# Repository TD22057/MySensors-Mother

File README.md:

# MySensors Mother/Daughter board system

This repository contains the PCB design files, 3D renderings, and
software libraries to implement the
[MySensors](http:www.mysensors.org) mother/daughter board system
[described in this
thread](http://forum.mysensors.org/topic/2480/mother-daughter-board-system).

It's a mother/daughter board design using an RFM69 radio (though it
would be easy to change it to an NRF). I have about 10 sensors I need
to make and they're all similar, but not quite the same. This system
allows be to mix and match what I need for each application. It's
designed to be AC powered and uses a single case (see below) for all
of them (~$3/apiece for 10).

The main board has the basic components and supports two daughter
boards (roughly 25mm x 35mm) which plug into the side so the whole
assembly is basically flat (leaving more room in the case for the
switches, connectors, and LED's). An additional third daughter board
can be used for small boards mounted perpendicular to the main boards
(the sensor board below does that) or mounting over the top of the
arduino.

The main board contains:

- 3.3V Arduino Pro Mini
- RFM69 radio
   - side mount for external dipole antenna
   - interior mount with enough space for a helical antenna mounted
     parallel or perpendicular to the board
- 5V->3.3V power supply
- digital signing chip
- flash memory chip
- input and output shift registers
- headers for a switch, LED, and piezo buzzer
- header for SPI (MISO, MOSI, SCK) pins
- 2 side mounted daughter board headers with inputs and outputs from
  the shift registers
- 1 top mounted daughter board header with pins from the mini including
  D3 (IRQ), D5 and D6 (PWM), A3, A4 (SDA), and A5 (SCL)
- all components are top mounted for easier soldering and a bigger
  ground plane for better antenna performance

# Boards

Each daughter board header has 5V, 3.3V, ground, 3 input pins, and 3
output pins.  I've designed seven different daughter boards so far.   

- Valve/motor control board. I'm using this for articulated water
  valves for controlling leaks at the water heater, washing machine,
  etc.  It contains a L9110 motor controller, LED, and valve
  open/closed sensors.
- AC relay board. I'm using this to control simple AC load switching
  (in my case, a recirculation pump).  The board contains an
  opto-isolated AC relay with NO and NC terminals, 1 LED, and 2 sensor
  inputs with pull down resistors.
- DC relay board. I'm using this to control simple DC load switching
  (in my case, a triggering a garage door).  The board contains an
  opto-isolated DC relay with NO and NC terminals, 2 LED's, and 3 sensor
  inputs with pull down resistors.
- Protected input board. I'm using this to trigger when external
  security cameras and motion sensors trip (they both operate on 12V
  signals).  The board contains 3 opto-isolator circuits for
  triggering on 12V lines.
- Parking/RGB sensor board.  This board contains pins for an
  ultrasonic distance sensor and an RGB (neopixel) ring.  It includes
  5V/3.3V level shifting for the distance sensor.  This board must be
  connected to the 3'rd slot which interfaces directly with the
  Arduino pins because of the neopixel timing requirements.
- Sensor board.  3 sensor inputs with pull down resistors and 3 LED
  outputs with 1K resistors.  This is designed primarily for water
  leak detectors.  The rope leak sensor I'm using works better w/ 5V
  input and analog output so sensors can be fed with 5V or 3.3V and
  when connected in the 3'rd slot, they will output to the Arduino's
  analog pins.
- I2C board.  This is simple small board that adds multiple I2C pins.

Here's an image of the assembled boards:

# Ordering

The boards file contains the individual board designs (done in Eagle)
as well as panelized versions.  A single 10cm x 10cm panel contains 2
main boards, 1 each of the AC relay, DC relay, protected input,
parking board, and I2C board; 2 valve boards; and 3 sensor boards.  

# Project Case

The boards are designed to fit inside a specific case (size and
mounting holes) which can be [found
here](http://www.aliexpress.com/item/Wholesale-electrical-junction-box-10pcs-105-65-40mm-plastic-instrument-box-plastic-box-electronic-project-box/1986580384.html).
There are many options for ordering this case on AliExpress (various
quantities and vendors).  Searching for ["105\*65\*40mm"](http://www.aliexpress.com/af/105*65*40mm.html?ltype=wholesale&d=y&origin=n&isViewCP=y&catId=0&initiative_id=SB_20160206141640&SearchText=105*65*40mm) will
generally show them all.

# Software

The lib directory contains a class for each board.  Each child board
class is constructed by passing it a structure from the main board
class which defines which slot it's plugged in to.  The boards (mother
and children) all contain elements for manipulating their components
(LED's, relays, sensors, etc) which abstract away the method by which
their connected (call sensor.led[0].on() to turn on the 0'th LED of a
sensor board) which makes writing the final sketches which use the
boards very easy.

The software does depend on my [arduino-core library
classes](https://github.com/TD22057/TD-Arduino-Core).

# Licenses

All the software in this repository is covered by the GPL-V3 license
(see [LICENSE-software](LICENSE-software)).

All the hardare in this repository is covered by the CERN Open
Hardware Licence v1.2 (see [LICENSE-hardware](LICENSE-hardware)).

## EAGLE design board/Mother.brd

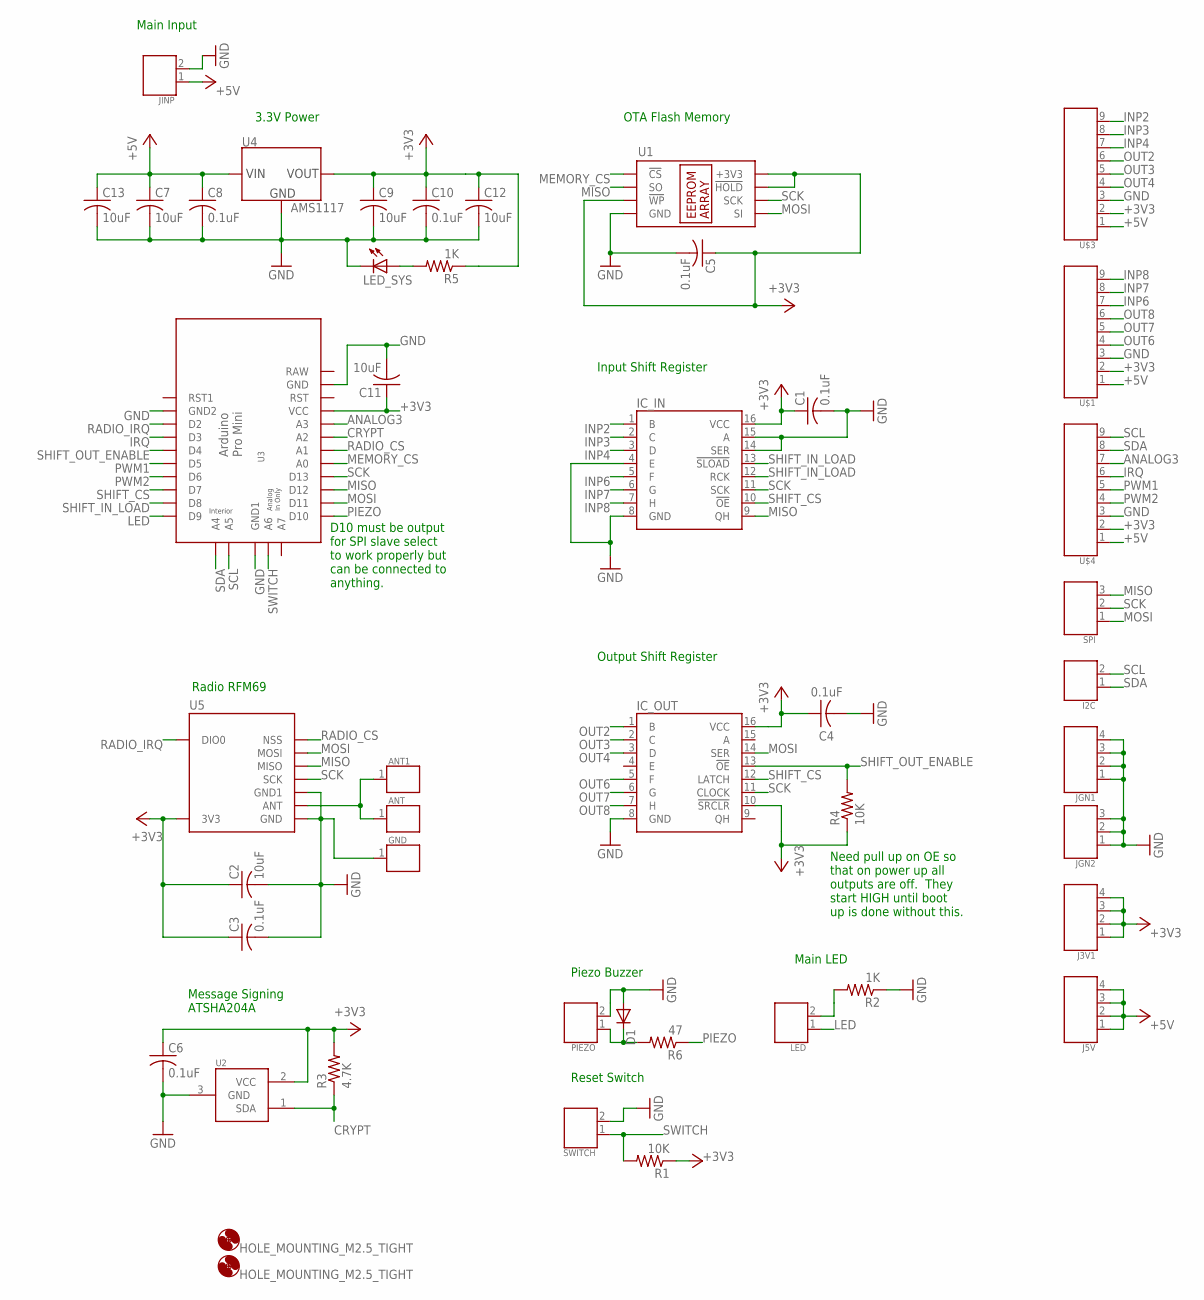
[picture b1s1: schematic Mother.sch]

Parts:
ANT, ANT1: CONNECTOR_1DUPONT; DUPONT_1
C1, C3, C4, C5, C6, C8, C10: 0.1uF; CAP_0805
C2, C7, C9, C11, C12, C13: 10uF; CAP_0805
D1: DIODESOD323; SOD323
GND: CONNECTOR_1DUPONT; DUPONT_1
H1, H2: HOLE_MOUNTING_M2.5_TIGHT; HOLE_M2.5PAN_TIGHT
I2C: CONNECTOR_2DUPONT; DUPONT_2
IC_IN: IC_MM74HC589SO16; SO16
IC_OUT: IC_SN74HC595; SO16
J3V1, J5V: CONNECTOR_4DUPONT; DUPONT_4
JGN1: CONNECTOR_4DUPONT; DUPONT_4
JGN2: CONNECTOR_3DUPONT; DUPONT_3
JINP: CONNECTOR_2DUPONT; DUPONT_2
LED: CONNECTOR_2DUPONT; DUPONT_2
LED_SYS: LED; LED_0805
PIEZO: CONNECTOR_2DUPONT; DUPONT_2
R1, R4: 10K; R_0805
R2, R5: 1K; R_0805
R3: 4.7K; R_0805
R6: 47; R_0805
SPI: CONNECTOR_3DUPONT; DUPONT_3
SWITCH: CONNECTOR_2DUPONT; DUPONT_2
U1: IC_EEPROM; SO-08
U2: IC_ATSHA204A_CRYPT; SOT23-3
U3: ARD_PRO_MINI_CLONE_NOPROG; PRO_MINI_CLONE_NO_PROG
U4: AMS1117; SOT223
U5: RADIO_RFM69W_MIN_PAD; RFM69W_MIN_PAD
U$1, U$3: CONNECTOR_9DUP_MALE90; DUPONT_MALE90_9
U$4: CONNECTOR_9DUPONT; DUPONT_9

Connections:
+3V3: C1.1, C2.1, C3.1, C4.1, C5.1, C6.1, C9.1, C10.1, C11.1, C12.1, IC_IN.16 (VCC), IC_OUT.10 (!SRCLR), IC_OUT.16 (VCC), J3V1.1, J3V1.2, J3V1.3, J3V1.4, R1.1, R3.2, R4.1, R5.1, U1.3 (!WP), U1.7 (!HOLD), U1.8 (+3V3), U2.2 (VCC), U3.P$19 (VCC), U4.2 (VOUT), U4.4 (VOUT), U5.8 (3V3), U$1.2, U$3.2, U$4.2
+5V: C7.1, C8.1, C13.1, J5V.1, J5V.2, J5V.3, J5V.4, JINP.1, U4.3 (VIN), U$1.1, U$3.1, U$4.1
ANALOG3: U3.P$18 (A3), U$4.7
CRYPT: R3.1, U2.1 (SDA), U3.P$17 (A2)
GND: C1.2, C2.2, C3.2, C4.2, C5.2, C6.2, C7.2, C8.2, C9.2, C10.2, C11.2, C12.2, C13.2, D1.A, GND.1, IC_IN.4 (E), IC_IN.8 (GND), IC_IN.14 (SER), IC_IN.15 (A), IC_OUT.8 (GND), JGN1.1, JGN1.2, JGN1.3, JGN1.4, JGN2.1, JGN2.2, JGN2.3, JINP.2, LED_SYS.2 (C), PIEZO.2, R2.1, SWITCH.2, U1.4 (GND), U2.3 (GND), U3.P$2 (GND2), U3.P$21 (GND), U3.P$27 (GND1), U4.1 (GND), U5.9 (GND), U5.11 (GND1), U$1.3, U$3.3, U$4.3
INP2: IC_IN.1 (B), U$3.9
INP3: IC_IN.2 (C), U$3.8
INP4: IC_IN.3 (D), U$3.7
INP6: IC_IN.5 (F), U$1.7
INP7: IC_IN.6 (G), U$1.8
INP8: IC_IN.7 (H), U$1.9
IRQ: U3.P$4 (D3), U$4.6
LED: LED.1, U3.P$10 (D9)
MEMORY_CS: U1.1 (!CS), U3.P$15 (A0)
MISO: IC_IN.9 (QH), SPI.3, U1.2 (SO), U3.P$13 (D12), U5.13 (MISO)
MOSI: IC_OUT.14 (SER), SPI.1, U1.5 (SI), U3.P$12 (D11), U5.14 (MOSI)
unnamed: LED.2, R2.2
unnamed: LED_SYS.1 (A), R5.2
unnamed: D1.C, PIEZO.1, R6.2
unnamed: ANT.1, ANT1.1, U5.10 (ANT)
OUT2: IC_OUT.1 (B), U$3.6
OUT3: IC_OUT.2 (C), U$3.5
OUT4: IC_OUT.3 (D), U$3.4
OUT6: IC_OUT.5 (F), U$1.4
OUT7: IC_OUT.6 (G), U$1.5
OUT8: IC_OUT.7 (H), U$1.6
PIEZO: R6.1, U3.P$11 (D10)
PWM1: U3.P$6 (D5), U$4.5
PWM2: U3.P$7 (D6), U$4.4
RADIO_CS: U3.P$16 (A1), U5.15 (NSS)
RADIO_IRQ: U3.P$3 (D2), U5.2 (DIO0)
RAW: U3.P$22 (RAW)
SCK: IC_IN.11 (SCK), IC_OUT.11 (CLOCK), SPI.2, U1.6 (SCK), U3.P$14 (D13), U5.12 (SCK)
SCL: I2C.2, U3.P$24 (A5), U$4.9
SDA: I2C.1, U3.P$23 (A4), U$4.8
SHIFT_CS: IC_IN.10 (!OE), IC_OUT.12 (LATCH), U3.P$8 (D7)
SHIFT_IN_LOAD: IC_IN.12 (RCK), IC_IN.13 (!SLOAD), U3.P$9 (D8)
SHIFT_OUT_ENABLE: IC_OUT.13 (!OE), R4.2, U3.P$5 (D4)
SWITCH: R1.2, SWITCH.1, U3.P$26 (A6)

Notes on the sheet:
Message Signing ATSHA204A
3.3V Power
Reset Switch
Input Shift Register
Piezo Buzzer
Radio RFM69
OTA Flash Memory
D10 must be output for SPI slave select to work properly but can be connected to anything.
Output Shift Register
Need pull up on OE so that on power up all outputs are off. They start HIGH until boot up is done without this.
Main LED
Main Input

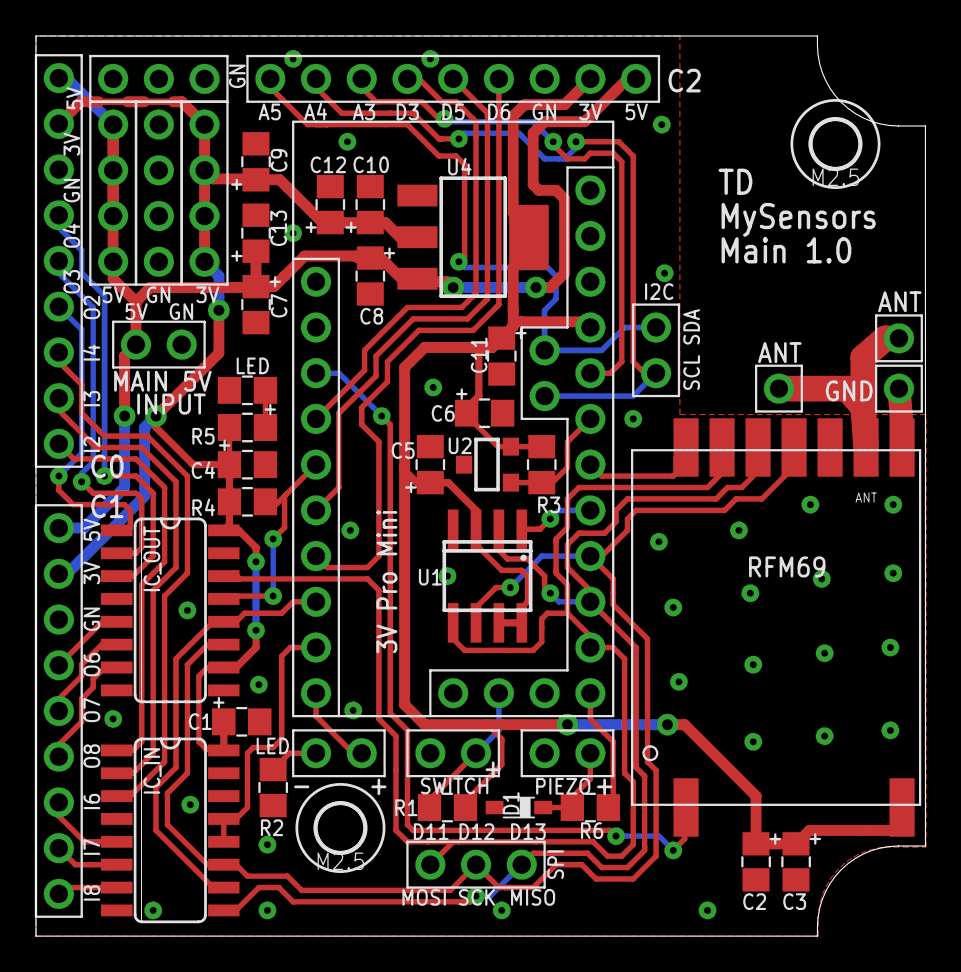
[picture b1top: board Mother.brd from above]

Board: 4 copper layers, 49.4 x 50.0 mm, 46 parts (0 on the bottom side), 38 nets.

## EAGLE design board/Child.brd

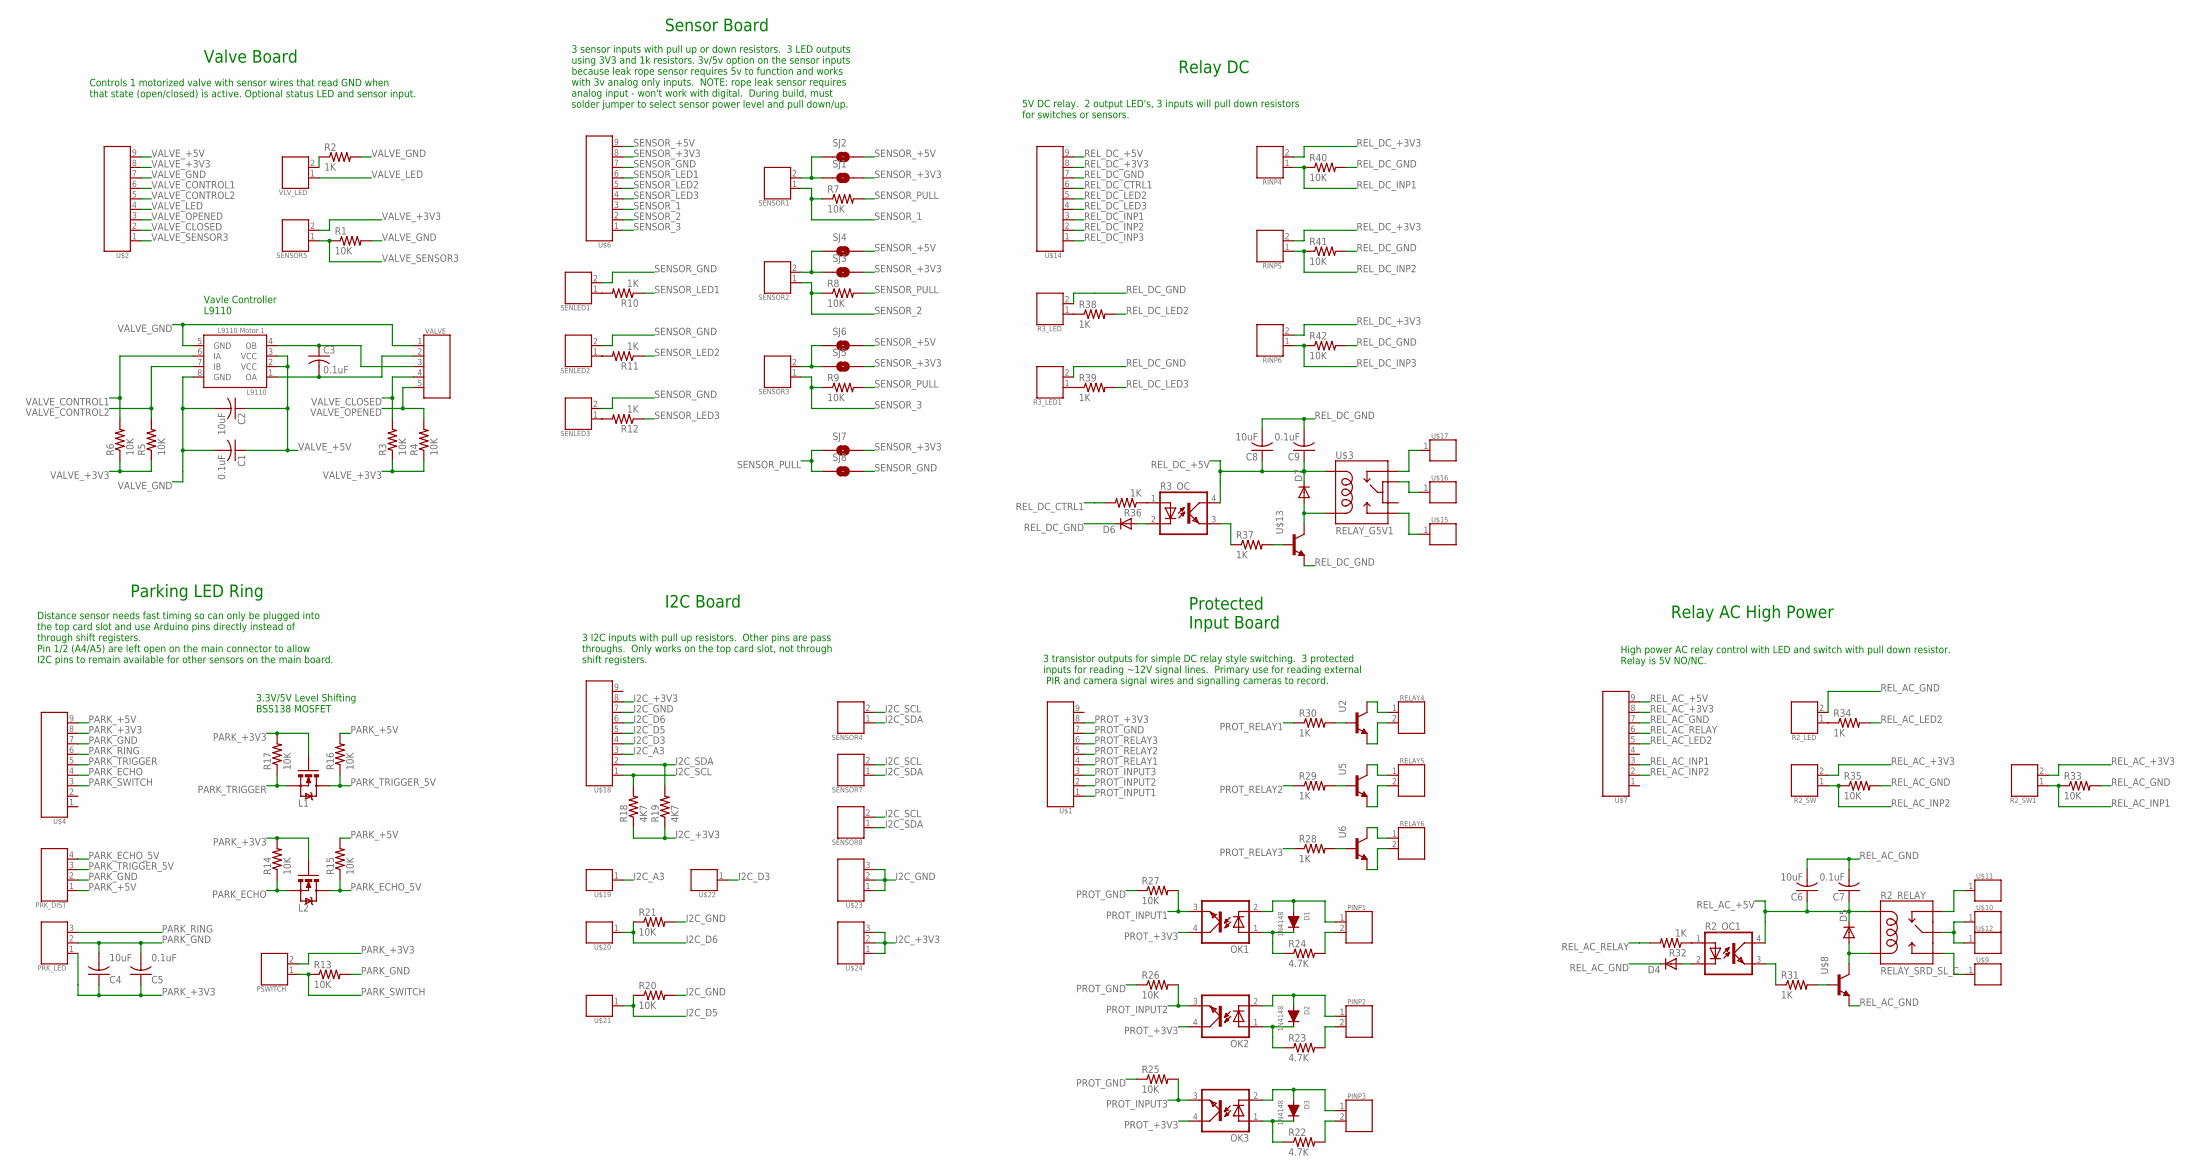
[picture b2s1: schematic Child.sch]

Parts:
C1, C3, C5, C7, C9: 0.1uF; CAP_0805
C2, C4, C6, C8: 10uF; CAP_0805
D1, D2, D3: 1N4148; SOD123
D4, D5, D6, D7: DIODESOD323; SOD323
L1, L2: MOSFET-NCHANNELSMD; SOT23-3
L9110: L9110 Motor 1; SO-08
OK1, OK2, OK3: PC817SOP; SO-4_PC817
PINP1, PINP2, PINP3: CONNECTOR_2DUPONT; DUPONT_2
PRK_DIST: CONNECTOR_4DUPONT; DUPONT_4
PRK_LED: CONNECTOR_3DUPONT; DUPONT_3
PSWITCH: CONNECTOR_2DUPONT; DUPONT_2
R1, R3, R4, R5, R6, R7, R8, R9, R13, R14, R15, R16, R17, R20, R21, R25, R26, R27, R33, R35, R40, R41, R42: 10K; R_0805
R2, R10, R11, R12, R28, R29, R30, R31, R32, R34, R36, R37, R38, R39: 1K; R_0805
R2_LED, R2_SW, R2_SW1, R3_LED, R3_LED1: CONNECTOR_2DUPONT; DUPONT_2
R2_OC1, R3_OC: PC817SOP; SO-4_PC817
R2_RELAY: RELAY_SRD_SL_C; RELAY_SRD-SL-C
R18, R19: 4K7; R_0805
R22, R23, R24: 4.7K; R_0805
RELAY4, RELAY5, RELAY6: CONNECTOR_2DUPONT; DUPONT_2
RINP4, RINP5, RINP6: CONNECTOR_2DUPONT; DUPONT_2
SENLED1, SENLED2, SENLED3: CONNECTOR_2DUPONT; DUPONT_2
SENSOR1, SENSOR2, SENSOR3, SENSOR4, SENSOR5, SENSOR7, SENSOR8: CONNECTOR_2DUPONT; DUPONT_2
SJ1, SJ2, SJ3, SJ4, SJ5, SJ6, SJ7, SJ8: JUMPER-PAD-2-NOYES_SILK; PAD-JUMPER-2-NO_YES_SILK
U2, U5, U6: TRANSISTORSMD; SOT23-3
U$1, U$2, U$6, U$7, U$14, U$18: CONNECTOR_9DUP_FEM90; DUPONT_FEM90_9
U$3: RELAY_G5V1; RELAY-G5V
U$4: CONNECTOR_9DUPONT; DUPONT_9
U$8, U$13: TRANSISTORSMD; SOT23-3
U$9, U$10, U$11, U$12: CONNECTOR_1DUP_LARGE; DUPONT_1_LRG
U$15, U$16, U$17, U$19, U$20, U$21, U$22: CONNECTOR_1DUPONT; DUPONT_1
U$23, U$24: CONNECTOR_3DUPONT; DUPONT_3
VALVE: CONNECTOR_5DUPONT; DUPONT_5
VLV_LED: CONNECTOR_2DUPONT; DUPONT_2

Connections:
I2C_+3V3: R18.1, R19.1, U$18.8, U$24.1, U$24.2, U$24.3
I2C_A3: U$18.3, U$19.1
I2C_D3: U$18.4, U$22.1
I2C_D5: R20.1, U$18.5, U$21.1
I2C_D6: R21.1, U$18.6, U$20.1
I2C_GND: R20.2, R21.2, U$18.7, U$23.1, U$23.2, U$23.3
I2C_SCL: R18.2, SENSOR4.2, SENSOR7.2, SENSOR8.2, U$18.1
I2C_SDA: R19.2, SENSOR4.1, SENSOR7.1, SENSOR8.1, U$18.2
unnamed: C3.1, L9110.4 (OB), VALVE.3
unnamed: C3.2, L9110.1 (OA), VALVE.2
unnamed: R2.1, VLV_LED.2
unnamed: D1.C (K), OK1.1, R24.1
unnamed: D1.A, OK1.2, PINP1.1
unnamed: PINP1.2, R24.2
unnamed: D2.C (K), OK2.1, R23.1
unnamed: D2.A, OK2.2, PINP2.1
unnamed: PINP2.2, R23.2
unnamed: D3.C (K), OK3.1, R22.1
unnamed: D3.A, OK3.2, PINP3.1
unnamed: PINP3.2, R22.2
unnamed: R10.2, SENLED1.1
unnamed: R11.2, SENLED2.1
unnamed: R12.2, SENLED3.1
unnamed: R30.2, U2.1 (BASE)
unnamed: RELAY4.1, U2.3 (COLLECTOR)
unnamed: RELAY4.2, U2.2 (EMITTER)
unnamed: SENSOR3.2, SJ5.1, SJ6.1
unnamed: SENSOR2.2, SJ3.1, SJ4.1
unnamed: R29.2, U5.1 (BASE)
unnamed: R28.2, U6.1 (BASE)
unnamed: R3_LED1.1, R39.1
unnamed: RELAY5.1, U5.3 (COLLECTOR)
unnamed: RELAY5.2, U5.2 (EMITTER)
unnamed: RELAY6.1, U6.3 (COLLECTOR)
unnamed: RELAY6.2, U6.2 (EMITTER)
unnamed: R2_LED.1, R34.1
unnamed: D5.A, R2_RELAY.2 (COIL_B), U$8.3 (COLLECTOR)
unnamed: R31.2, U$8.1 (BASE)
unnamed: R2_OC1.3 (EMIT), R31.1
unnamed: D4.A, R2_OC1.2
unnamed: R2_OC1.1, R32.1
unnamed: D7.A, U$3.9, U$13.3 (COLLECTOR)
unnamed: R37.2, U$13.1 (BASE)
unnamed: R3_OC.3 (EMIT), R37.1
unnamed: D6.A, R3_OC.2
unnamed: R3_OC.1, R36.1
unnamed: R3_LED.1, R38.1
unnamed: U$3.5, U$16.1
unnamed: SENSOR1.2, SJ1.1, SJ2.1
PARK_+3V3: C4.1, C5.1, L1.1 (G), L2.1 (G), PRK_LED.1, PSWITCH.2, R14.2, R17.2, U$4.8
PARK_+5V: PRK_DIST.1, R15.2, R16.2, U$4.9
PARK_ECHO: L2.2 (S), R14.1, U$4.4
PARK_ECHO_5V: L2.3 (D), PRK_DIST.4, R15.1
PARK_GND: C4.2, C5.2, PRK_DIST.2, PRK_LED.2, R13.2, U$4.7
PARK_RING: PRK_LED.3, U$4.6
PARK_SWITCH: PSWITCH.1, R13.1, U$4.3
PARK_TRIGGER: L1.2 (S), R17.1, U$4.5
PARK_TRIGGER_5V: L1.3 (D), PRK_DIST.3, R16.1
PROT_+3V3: OK1.4 (COL), OK2.4 (COL), OK3.4 (COL), U$1.8
PROT_GND: R25.1, R26.1, R27.1, U$1.7
PROT_INPUT1: OK1.3 (EMIT), R27.2, U$1.1
PROT_INPUT2: OK2.3 (EMIT), R26.2, U$1.2
PROT_INPUT3: OK3.3 (EMIT), R25.2, U$1.3
PROT_RELAY1: R30.1, U$1.4
PROT_RELAY2: R29.1, U$1.5
PROT_RELAY3: R28.1, U$1.6
R2_COM: R2_RELAY.3 (COM), U$10.1, U$12.1
R2_NC: R2_RELAY.5 (NC), U$11.1
R2_NC1: U$3.1, U$17.1
R2_NO: R2_RELAY.4 (NO), U$9.1
R2_NO1: U$3.10, U$15.1
REL_AC_+3V3: R2_SW.2, R2_SW1.2, U$7.8
REL_AC_+5V: C6.1, C7.1, D5.C, R2_OC1.4 (COL), R2_RELAY.1 (COIL_A), U$7.9
REL_AC_GND: C6.2, C7.2, D4.C, R2_LED.2, R33.2, R35.2, U$7.7, U$8.2 (EMITTER)
REL_AC_INP1: R2_SW1.1, R33.1, U$7.3
REL_AC_INP2: R2_SW.1, R35.1, U$7.2
REL_AC_LED2: R34.2, U$7.5
REL_AC_RELAY: R32.2, U$7.6
REL_DC_+3V3: RINP4.2, RINP5.2, RINP6.2, U$14.8
REL_DC_+5V: C8.1, C9.1, D7.C, R3_OC.4 (COL), U$3.2, U$14.9
REL_DC_CTRL1: R36.2, U$14.6
REL_DC_GND: C8.2, C9.2, D6.C, R3_LED.2, R3_LED1.2, R40.2, R41.2, R42.2, U$13.2 (EMITTER), U$14.7
REL_DC_INP1: R40.1, RINP4.1, U$14.3
REL_DC_INP2: R41.1, RINP5.1, U$14.2
REL_DC_INP3: R42.1, RINP6.1, U$14.1
REL_DC_LED2: R38.2, U$14.5
REL_DC_LED3: R39.2, U$14.4
SENSOR_1: R7.1, SENSOR1.1, U$6.3
SENSOR_2: R8.1, SENSOR2.1, U$6.2
SENSOR_3: R9.1, SENSOR3.1, U$6.1
SENSOR_+3V3: SJ1.2, SJ3.2, SJ5.2, SJ7.2, U$6.8
SENSOR_+5V: SJ2.2, SJ4.2, SJ6.2, U$6.9
SENSOR_GND: SENLED1.2, SENLED2.2, SENLED3.2, SJ8.2, U$6.7
SENSOR_LED1: R10.1, U$6.6
SENSOR_LED2: R11.1, U$6.5
SENSOR_LED3: R12.1, U$6.4
SENSOR_PULL: R7.2, R8.2, R9.2, SJ7.1, SJ8.1
VALVE_+3V3: R3.1, R4.1, R5.1, R6.1, SENSOR5.2, U$2.8
VALVE_+5V: C1.1, C2.1, L9110.2 (VCC), L9110.3 (VCC), U$2.9
VALVE_CLOSED: R3.2, U$2.2, VALVE.4
VALVE_CONTROL1: L9110.6 (IA), R6.2, U$2.6
VALVE_CONTROL2: L9110.7 (IB), R5.2, U$2.5
VALVE_GND: C1.2, C2.2, L9110.5 (GND), L9110.8 (GND), R1.2, R2.2, U$2.7, VALVE.1
VALVE_LED: U$2.4, VLV_LED.1
VALVE_OPENED: R4.2, U$2.3, VALVE.5
VALVE_SENSOR3: R1.1, SENSOR5.1, U$2.1

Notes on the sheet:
Vavle Controller L9110
Valve Board
Protected Input Board
Sensor Board
3.3V/5V Level Shifting BSS138 MOSFET
Parking LED Ring
Distance sensor needs fast timing so can only be plugged into the top card slot and use Arduino pins directly instead of through shift registers. Pin 1/2 (A4/A5) are left open on the main connector to allow I2C pins to remain available for other sensors on the main board.
Relay AC High Power
Relay DC
I2C Board
Controls 1 motorized valve with sensor wires that read GND when that state (open/closed) is active. Optional status LED and sensor input.
3 sensor inputs with pull up or down resistors. 3 LED outputs using 3V3 and 1k resistors. 3v/5v option on the sensor inputs because leak rope sensor requires 5v to function and works with 3v analog only inputs. NOTE: rope leak sensor requires analog input - won't work with digital. During build, mu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
3 I2C inputs with pull up resistors. Other pins are pass throughs. Only works on the top card slot, not through shift registers.
High power AC relay control with LED and switch with pull down resistor. Relay is 5V NO/NC.
5V DC relay. 2 output LED's, 3 inputs will pull down resistors for switches or sensors.
3 transistor outputs for simple DC relay style switching. 3 protected inputs for reading ~12V signal lines. Primary use for reading external PIR and camera signal wires and signalling cameras to record.

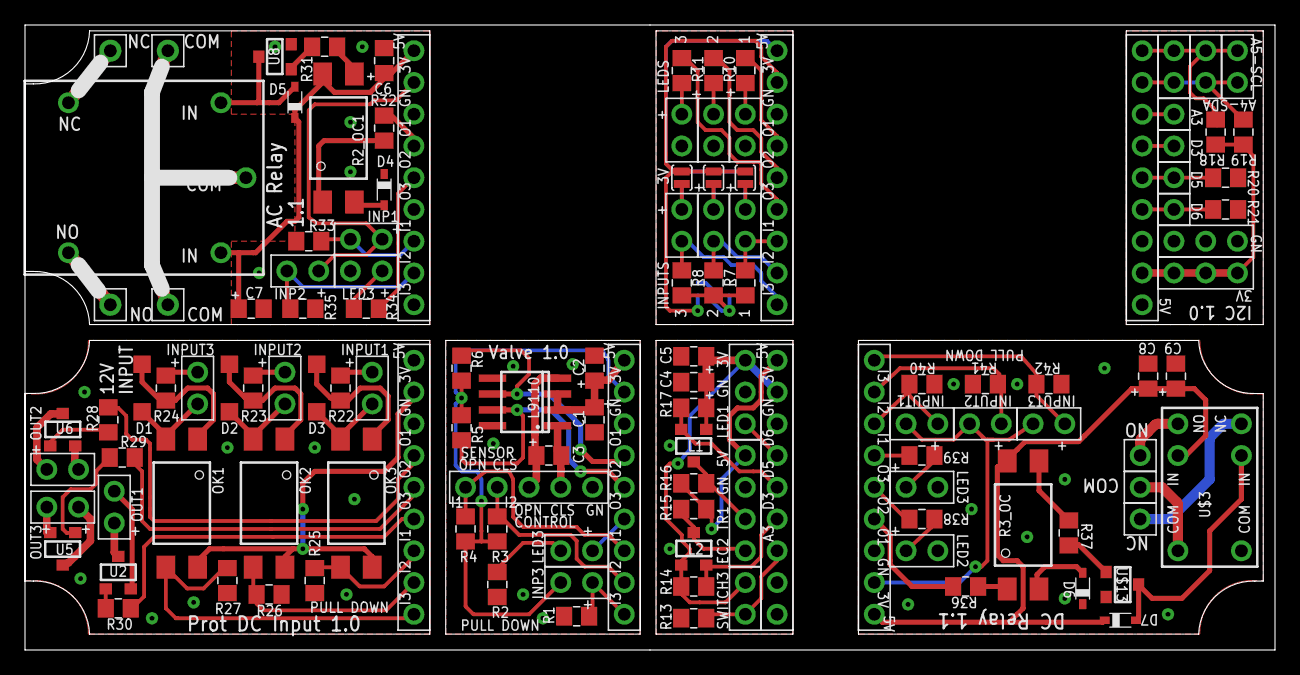
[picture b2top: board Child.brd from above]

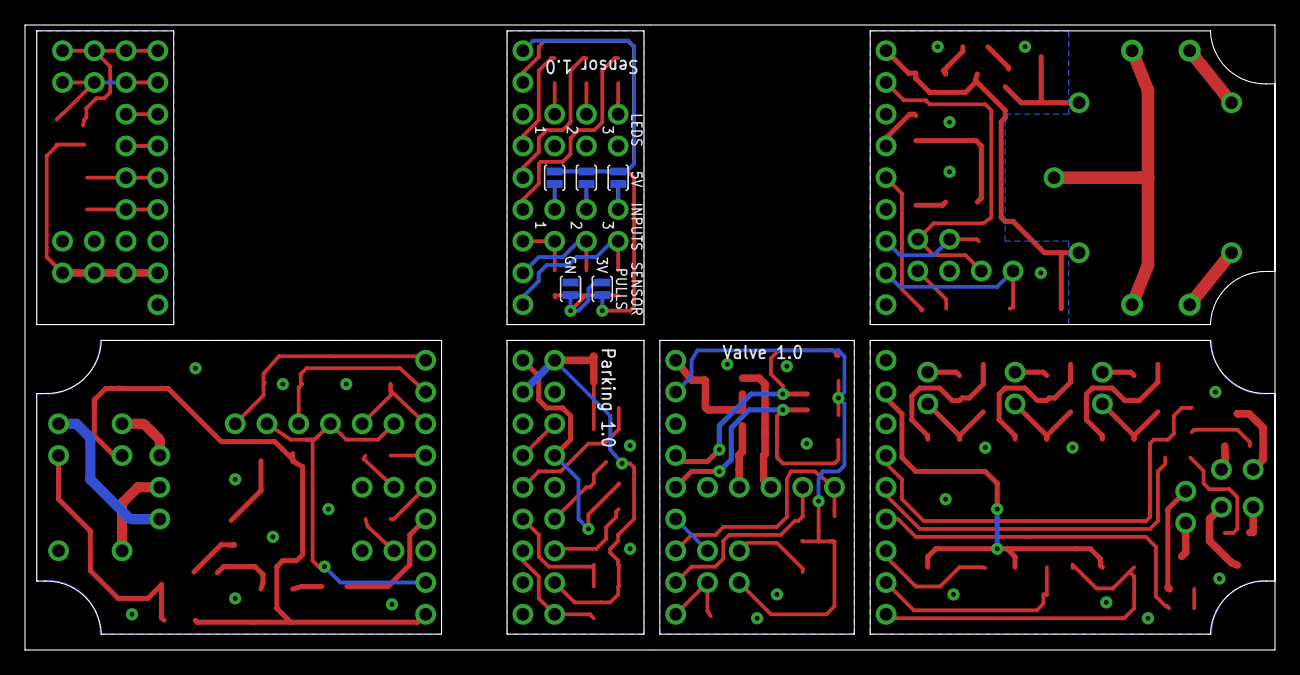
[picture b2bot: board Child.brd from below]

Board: 4 copper layers, 100.0 x 50.0 mm, 130 parts (5 on the bottom side), 106 nets.

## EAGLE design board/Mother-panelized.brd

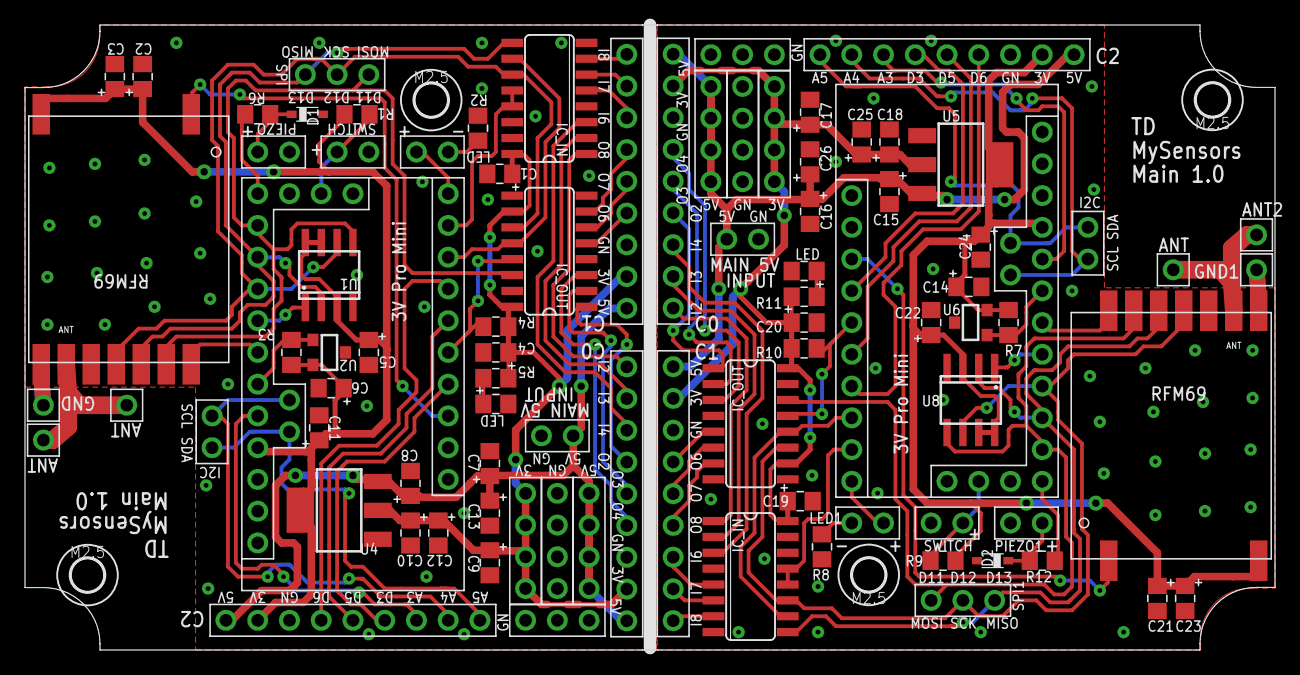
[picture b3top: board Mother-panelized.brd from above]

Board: 4 copper layers, 100.0 x 50.0 mm, 92 parts (0 on the bottom side), 76 nets.

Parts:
ANT, ANT1, ANT2, ANT3: DUPONT_1
C1, C3, C4, C5, C6, C8, C10, C14, C15, C18, C19, C20, C22, C23: 0.1uF; CAP_0805
C2, C7, C9, C11, C12, C13, C16, C17, C21, C24, C25, C26: 10uF; CAP_0805
D1, D2: SOD323
GND, GND1: DUPONT_1
H1, H2, H3, H4: HOLE_MOUNTING_M2.5_TIGHT; HOLE_M2.5PAN_TIGHT
I2C, I2C1: DUPONT_2
IC_IN, IC_IN1: SO16
IC_OUT, IC_OUT1: SO16
J3V1, J3V2, J5V, J5V1: DUPONT_4
JGN1, JGN4: DUPONT_4
JGN2, JGN3: DUPONT_3
JINP, JINP1: DUPONT_2
LED, LED1: DUPONT_2
LED_SYS, LED_SYS1: LED_0805
PIEZO, PIEZO1: DUPONT_2
R1, R4, R9, R10: 10K; R_0805
R2, R5, R8, R11: 1K; R_0805
R3, R7: 4.7K; R_0805
R6, R12: 220; R_0805
SPI, SPI1: DUPONT_3
SWITCH, SWITCH1: DUPONT_2
U1, U8: SO-08
U2, U6: SOT23-3
U3, U7: PRO_MINI_CLONE
U4, U5: AMS1117; SOT223
U$1, U$3, U$6, U$7: DUPONT_MALE90_9
U$2, U$5: RADIO_RFM69W_MS; RFM69W_MS
U$4, U$8: DUPONT_9

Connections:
+3V1: C14.1, C17.1, C18.1, C19.1, C20.1, C21.1, C22.1, C23.1, C24.1, C25.1, IC_IN1.16, IC_OUT1.10, IC_OUT1.16, J3V2.1, J3V2.2, J3V2.3, J3V2.4, R7.2, R9.1, R10.1, R11.1, U5.2, U5.4, U6.2, U7.P$19, U8.3, U8.7, U8.8, U$5.8, U$6.2, U$7.2, U$8.2
+3V3: C1.1, C2.1, C3.1, C4.1, C5.1, C6.1, C9.1, C10.1, C11.1, C12.1, IC_IN.16, IC_OUT.10, IC_OUT.16, J3V1.1, J3V1.2, J3V1.3, J3V1.4, R1.1, R3.2, R4.1, R5.1, U1.3, U1.7, U1.8, U2.2, U3.P$19, U4.2, U4.4, U$1.2, U$2.8, U$3.2, U$4.2
+5V: C7.1, C8.1, C13.1, J5V.1, J5V.2, J5V.3, J5V.4, JINP.1, U4.3, U$1.1, U$3.1, U$4.1
+5V1: C15.1, C16.1, C26.1, J5V1.1, J5V1.2, J5V1.3, J5V1.4, JINP1.1, U5.3, U$6.1, U$7.1, U$8.1
ANALOG1: U7.P$18, U$8.7
ANALOG3: U3.P$18, U$4.7
CRYPT: R3.1, U2.1, U3.P$17
CRYPT1: R7.1, U6.1, U7.P$17
GND: C1.2, C2.2, C3.2, C4.2, C5.2, C6.2, C7.2, C8.2, C9.2, C10.2, C11.2, C12.2, C13.2, D1.A, GND.1, IC_IN.4, IC_IN.8, IC_IN.14, IC_IN.15, IC_OUT.8, JGN1.1, JGN1.2, JGN1.3, JGN1.4, JGN2.1, JGN2.2, JGN2.3, JINP.2, LED_SYS.2, PIEZO.2, R2.1, SWITCH.2, U1.4, U2.3, U3.P$2, U3.P$21, U3.P$27, U4.1, U$1.3, U$2.9, U$2.11, U$3.3, U$4.3
GND1: C14.2, C15.2, C16.2, C17.2, C18.2, C19.2, C20.2, C21.2, C22.2, C23.2, C24.2, C25.2, C26.2, D2.A, GND1.1, IC_IN1.4, IC_IN1.8, IC_IN1.14, IC_IN1.15, IC_OUT1.8, JGN3.1, JGN3.2, JGN3.3, JGN4.1, JGN4.2, JGN4.3, JGN4.4, JINP1.2, LED_SYS1.2, PIEZO1.2, R8.1, SWITCH1.2, U5.1, U6.3, U7.P$2, U7.P$21, U7.P$27, U8.4, U$5.9, U$5.11, U$6.3, U$7.3, U$8.3
INP1: IC_IN1.5, U$6.7
INP2: IC_IN.1, U$3.9
INP3: IC_IN.2, U$3.8
INP4: IC_IN.3, U$3.7
INP5: IC_IN1.7, U$6.9
INP6: IC_IN.5, U$1.7
INP7: IC_IN.6, U$1.8
INP8: IC_IN.7, U$1.9
INP9: IC_IN1.3, U$7.7
INP10: IC_IN1.1, U$7.9
INP11: IC_IN1.6, U$6.8
INP12: IC_IN1.2, U$7.8
IRQ: U3.P$4, U$4.6
IRQ1: U7.P$4, U$8.6
LED: LED.1, U3.P$10
LED1: LED1.1, U7.P$10
MEMORY_CS: U1.1, U3.P$15
MEMORY_CS1: U7.P$15, U8.1
MISO: IC_IN.9, SPI.3, U1.2, U3.P$13, U$2.13
MISO1: IC_IN1.9, SPI1.3, U7.P$13, U8.2, U$5.13
MOSI: IC_OUT.14, SPI.1, U1.5, U3.P$12, U$2.14
MOSI1: IC_OUT1.14, SPI1.1, U7.P$12, U8.5, U$5.14
unnamed: LED.2, R2.2
unnamed: LED_SYS.1, R5.2
unnamed: D1.C, PIEZO.1, R6.2
unnamed: ANT2.1, ANT3.1, U$5.10
unnamed: LED1.2, R8.2
unnamed: LED_SYS1.1, R11.2
unnamed: D2.C, PIEZO1.1, R12.2
unnamed: ANT.1, ANT1.1, U$2.10
OUT1: IC_OUT1.1, U$7.6
OUT2: IC_OUT.1, U$3.6
OUT3: IC_OUT.2, U$3.5
OUT4: IC_OUT.3, U$3.4
OUT5: IC_OUT1.2, U$7.5
OUT6: IC_OUT.5, U$1.4
OUT7: IC_OUT.6, U$1.5
OUT8: IC_OUT.7, U$1.6
OUT9: IC_OUT1.3, U$7.4
OUT10: IC_OUT1.5, U$6.4
OUT11: IC_OUT1.7, U$6.6
OUT12: IC_OUT1.6, U$6.5
PIEZO: R6.1, U3.P$11
PIEZO1: R12.1, U7.P$11
PWM1: U3.P$6, U$4.5
PWM2: U3.P$7, U$4.4
PWM3: U7.P$7, U$8.4
PWM4: U7.P$6, U$8.5
RADIO_CS: U3.P$16, U$2.15
RADIO_CS1: U7.P$16, U$5.15
RADIO_IRQ: U3.P$3, U$2.2
RADIO_IRQ1: U7.P$3, U$5.2
SCK: IC_IN.11, IC_OUT.11, SPI.2, U1.6, U3.P$14, U$2.12
SCK1: IC_IN1.11, IC_OUT1.11, SPI1.2, U7.P$14, U8.6, U$5.12
SCL: I2C.2, U3.P$24, U$4.9
SCL1: I2C1.2, U7.P$24, U$8.9
SDA: I2C.1, U3.P$23, U$4.8
SDA1: I2C1.1, U7.P$23, U$8.8
SHIFT_CS: IC_IN.10, IC_OUT.12, U3.P$8
SHIFT_CS1: IC_IN1.10, IC_OUT1.12, U7.P$8
SHIFT_IN_LOAD: IC_IN.12, IC_IN.13, U3.P$9
SHIFT_IN_LOAD1: IC_IN1.12, IC_IN1.13, U7.P$9
SHIFT_OUT_ENABLE: IC_OUT.13, R4.2, U3.P$5
SHIFT_OUT_ENABLE1: IC_OUT1.13, R10.2, U7.P$5
SWITCH: R1.2, SWITCH.1, U3.P$26
SWITCH1: R9.2, SWITCH1.1, U7.P$26
